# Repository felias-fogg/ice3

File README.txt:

This Arduino sketch implements a cache thermometer, as for example
used in these geocaches:
- http://coord.info/GC3NEYY
- http://coord.info/GC47429
- http://coord.info/GC36NCQ

The generic hardware is sketched in the files open-V2-board.tiff and 
open-V2-plan.tiff. For the particular case of a thermometer, a DS18S20
and a LED is added in the prototyping section of the board. 

In order to compile and burn the sketch to the ATtiny84, one has to
make a few additions and modifications to the Arduino IDE and one
either has to use an existing UNO board as an ISP programmer or one
has to buy such a programmer, e.g., a USBtinyISP, see
http://www.amazon.com/HOSSEN%C2%AE-USBtinyISP-Programmer-Arduino-Bootloader/dp/B00CR9UGZQ/ref=sr_1_5.

First of all, one needs to extend the Arduino IDE to deal with
ATtiny processors. This is described in detail here:
http://hlt.media.mit.edu/?p=1695.

In order to compile the ice3 sketch, you need the OneWire
library. Note that the original library will not work here, because we
want the ATtiny to run with 1MHz. So download and install this library instead: https://github.com/felias-fogg/OneWire.

Now you should be able to compile the sketch. Please select ATtiny84
(internal 1 MHz) before doing so. By the way, if the ATtiny has been
used before, perhaps some fuses have to be set. In particular the one
for the processor speed. This can be done by pretending to upload the
bootloader. If it is a brand new processor or the one from an existing
ice3 board, the fuses will have been set to 1 MHz already.

Finally, you should be able to burn the program to the chip. Before
doing so remove the jumper that provides power to the board.  Plug the
6-pin ISP connector to the PCB such that the nose of the connector is
oriented towards the battery. Select the right programmer in the Tools
menu and select also the right serial port. Then you can use the
upload button to burn the program to the chip.

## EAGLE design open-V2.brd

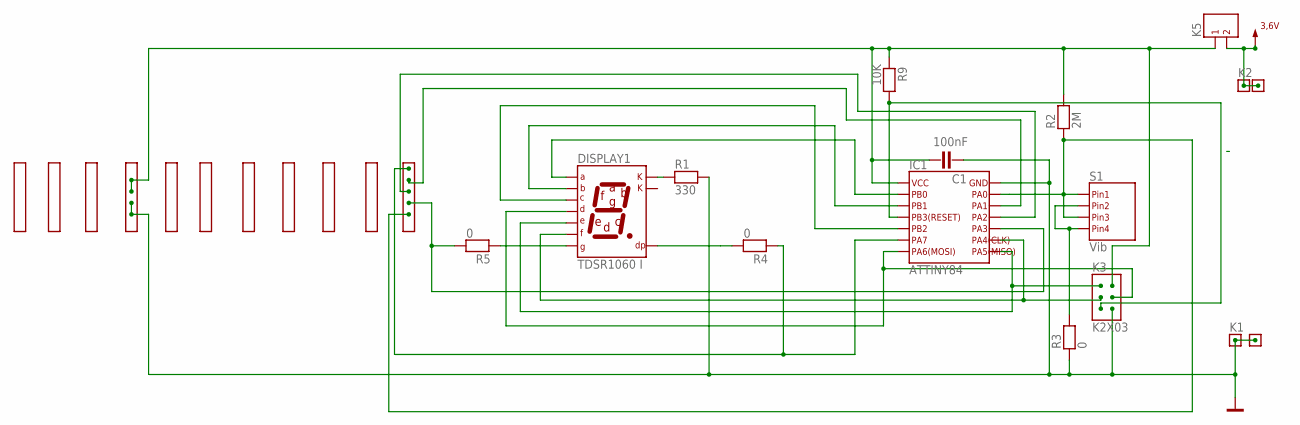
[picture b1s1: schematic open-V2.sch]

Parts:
C1: 100nF; C1
DISPLAY1: TDSR1060 I; DISPLAY1
IC1: ATTINY84; IC1
K1: K1
K2: K2
K3: K2X03; K3
K4: K4
K5: K5
K6: K6
K7: K7
K8: K8
K9: K9
K10: K10
K11: K11
K12: K12
K13: K13
K14: K14
K15: K15
K16: K16
K18: K18
R1: 330; R1
R2: 2M; R2
R3: 0; R3
R4: 0; R4
R5: 0; R5
R9: 10K; R9
S1: Vib; S1

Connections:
1: DISPLAY1.1 (G), R5.1
3,6V: K2.1, K5.2, K18.1
A: DISPLAY1.10 (A), IC1.2 (PB0)
B: DISPLAY1.9 (B), IC1.3 (PB1)
C: DISPLAY1.7 (C), IC1.5 (PB2)
D/MOSI: DISPLAY1.5 (D), IC1.7 (PA6(MOSI)), K3.4
DP: DISPLAY1.6 (DP), R4.2
E/MISO: DISPLAY1.4 (E), IC1.8 (PA5(MISO)), K3.1
F/CLK: DISPLAY1.2 (F), IC1.9 (PA4(CLK)), K3.3
G: IC1.10 (PA3), K10.3, R5.2
GND: C1.1, IC1.14 (GND), K1.1, K3.6, K13.2, K13.3, K16.1, R1.2, R3.1
K: DISPLAY1.3 (K), R1.1
PA0: IC1.13 (PA0), K10.2, R2.1, S1.1 (PIN1), S1.3 (PIN3)
PA1: IC1.12 (PA1), K10.5
PA2: IC1.11 (PA2), K10.4
PA7: IC1.6 (PA7), K10.6, R4.1
RST: IC1.4 (PB3(RESET)), K3.5, R9.2
SIG$25: R3.2, S1.2 (PIN2), S1.4 (PIN4)
VCC: C1.2, IC1.1 (VCC), K3.2, K5.1, K13.4, K13.5, R2.2, R9.1

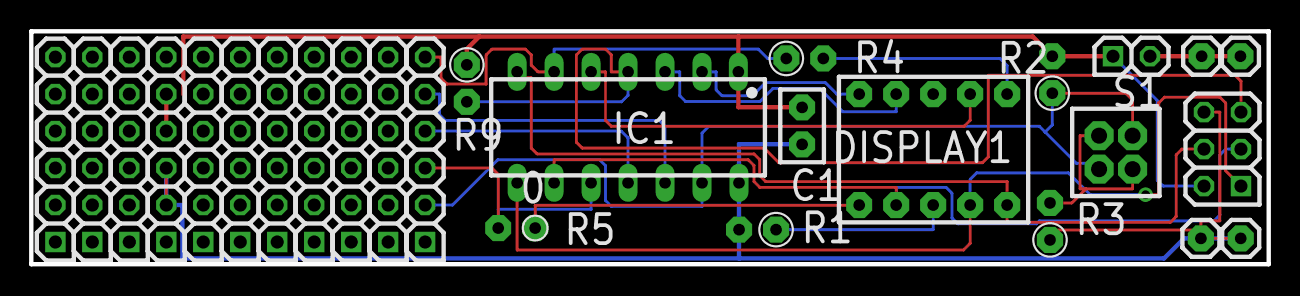
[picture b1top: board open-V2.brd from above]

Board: 2 copper layers, 85.0 x 16.0 mm, 27 parts (0 on the bottom side), 19 nets.

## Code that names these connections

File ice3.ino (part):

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*/
/* Display
   Seg	AVR-Pin Ard#(Attiny) Ard#(ProMini)
   a(10) -  PA6   6          8
   b(9)  -  PA5   5          7
   c(7)  -  PA4   4          6
   d(5)  -  PB0  10         12
   e(4)  -  PB1   9         11
   f(2)  -  PB2   8         10
   g(1)  -  PA2   2          4
   dp(6) -  PA3   3          5
*/
/* Other connections
   Bez          Ard#(Attikny) Ard#(ProMini)
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
/* Connections Open-v2:
   Seg	AVR-Pin Ard#(Attiny) Ard#(ProMini)
   a(10) -  PA6   6          8
   b(9)  -  PA5   5          7
   c(7)  -  PA4   4          6
   d(5)  -  PB0  10         12
   e(4)  -  PB1   9         11
   f(2)  -  PB2   8         10
   g(1)  -  PA7   7          9
   dp(6) -  PA3   3          5

   ID          Ard#(Attiny) Ard#(ProMini)
   Vib             0             2
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   R9: 10K
   C1: 100nF
   DS1820 Pin1: GND
   DS1820 Pin2: 4,7 kOhm to Vcc and connect to D1 (PA1) = Pin5 of connector
   DS1820 Pin3: Vcc
   LED Anode to Pin4 of connector
   
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  PCMSK1 |= (1<<PCINT8); // on pin PC0 = ADC0 = PCINT8 = analog0 = dig. pin 14
#endif 
#ifdef ATTINY
  GIMSK |= (1<<PCIE0);  // allow for PCINT on PA0-PA7
  PCMSK0 |= (1<<PCINT0); // on pin PA0 = ADC0 = analog0 = dig. pin 0
#endif
}

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
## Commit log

2017-02-12 Comments edited and schema and board file added
2017-03-21 added __attribute__((used)) to wdt_init
